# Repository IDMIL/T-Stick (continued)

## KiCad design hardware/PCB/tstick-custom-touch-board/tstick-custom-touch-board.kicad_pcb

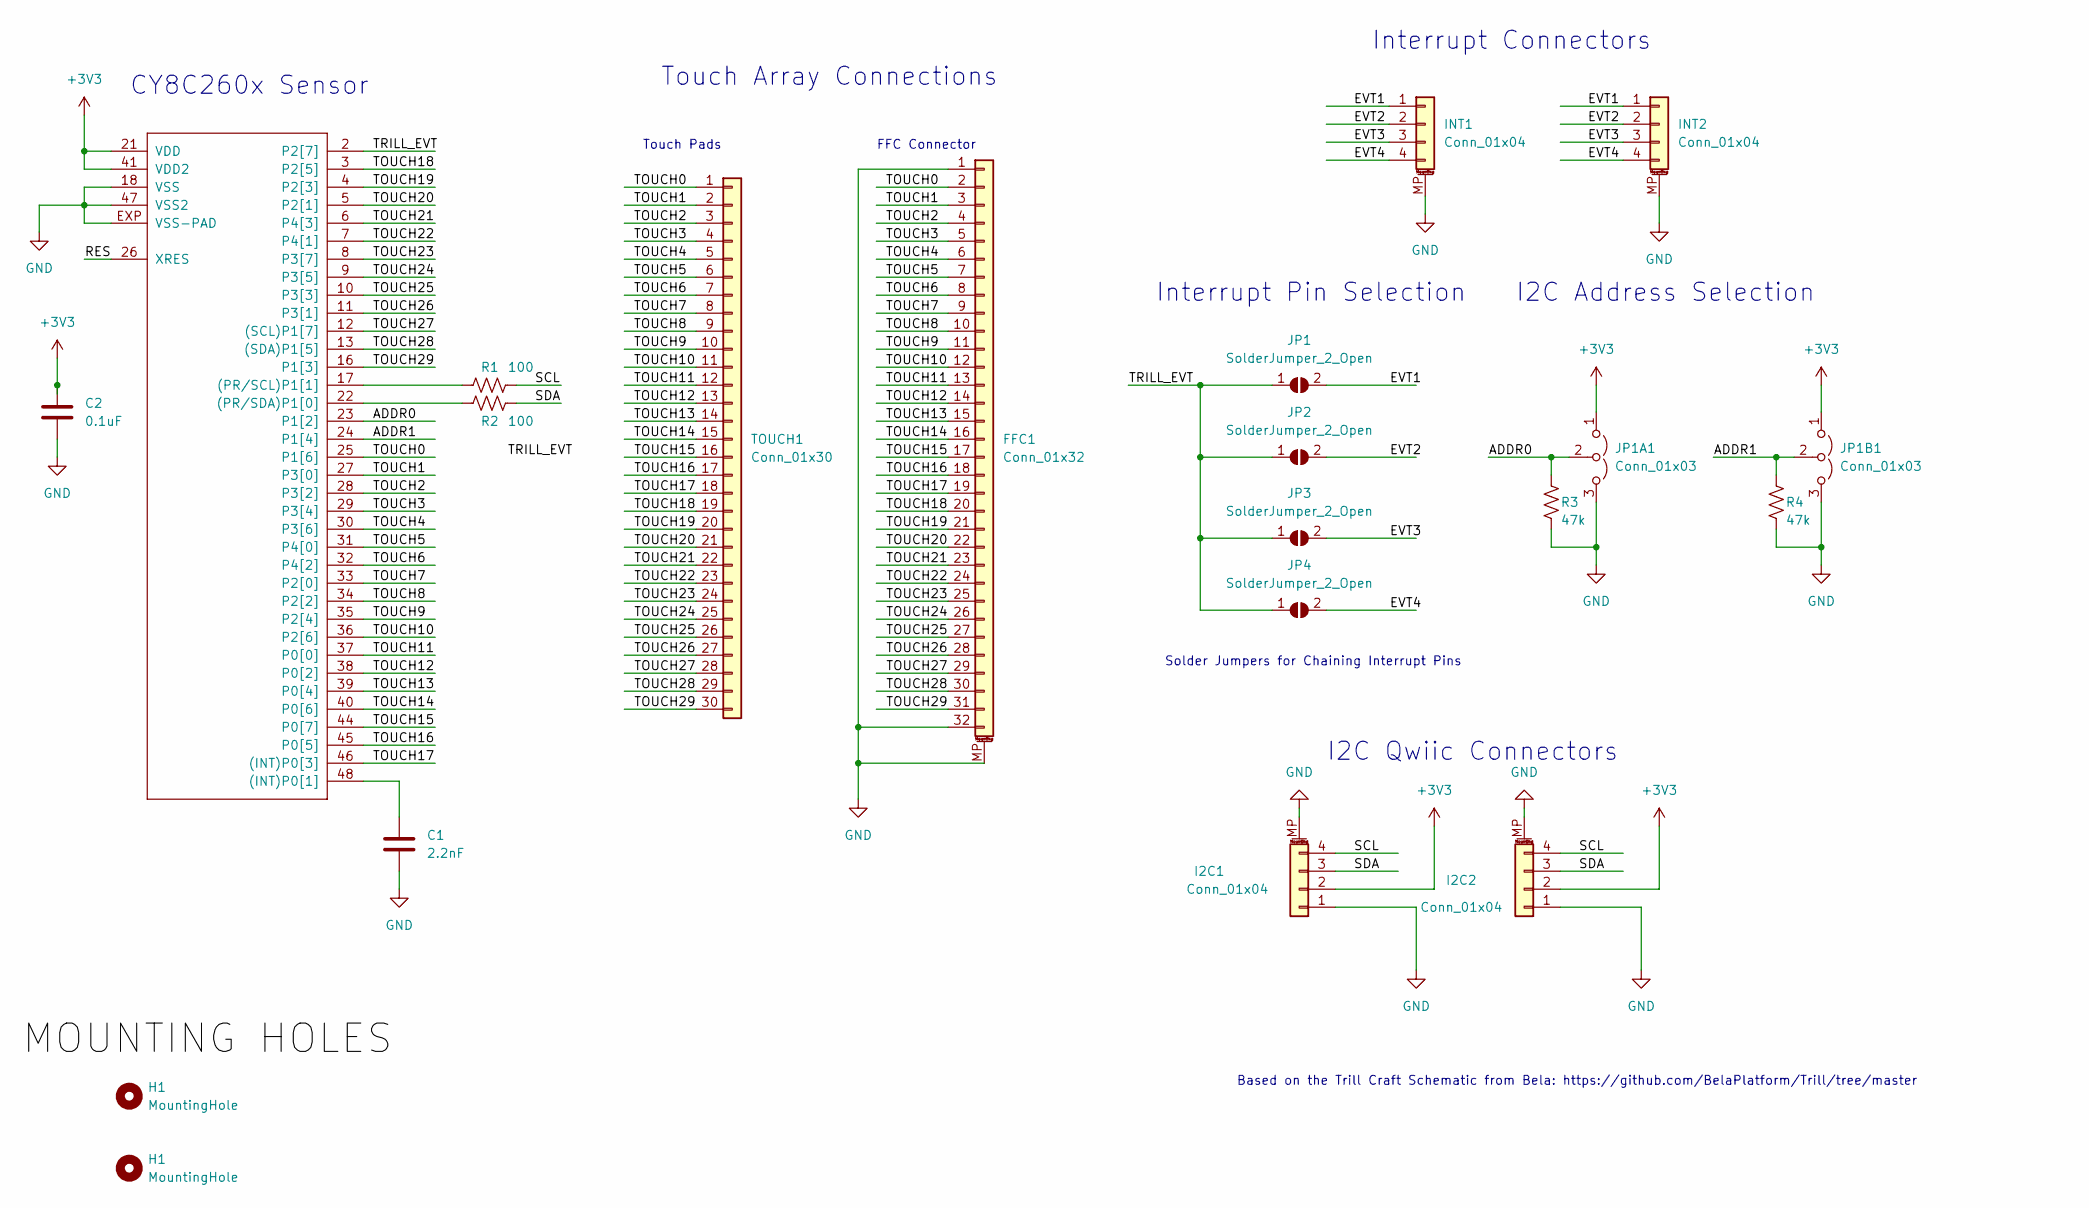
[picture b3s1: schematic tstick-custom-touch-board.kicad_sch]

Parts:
C1: 2.2nF; C_0603_1608Metric
C2: 0.1uF; C_0603_1608Metric
FFC1: Conn_01x32; CON_541323262_MOL; Mfg Part # 0541323262; Digikey Part # 900-0541323262CT-ND
H1: MountingHole; MountingHole_3.2mm_M3_DIN965
I2C1, I2C2: Conn_01x04; JST_SH_SM04B-SRSS-TB_1x04-1MP_P1.00mm_Horizontal
IC1: CY8C206X6A; QFN48-LEADS
INT1, INT2: Conn_01x04; JST_SH_SM04B-SRSS-TB_1x04-1MP_P1.00mm_Horizontal
JP1, JP2, JP3, JP4: SolderJumper_2_Open; SolderJumper-2_P1.3mm_Open_RoundedPad1.0x1.5mm
JP1A1, JP1B1: Conn_01x03; DOUBLE_SOLDER_JUMPER
R1, R2: 100; R_0603_1608Metric
R3, R4: 47k; R_0603_1608Metric
TOUCH1: Conn_01x30; TOUCHSENSORPAD; Mfg Part # 0541323262; Digikey Part # 900-0541323262CT-ND

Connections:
+3V3: C2.1, I2C1.2, I2C2.2, IC1.21 (VDD), IC1.41 (VDD2), JP1A1.1 (A), JP1B1.1 (A)
/ADDR0: IC1.23 (P1[2]), JP1A1.2 (C), R3.1
/ADDR1: IC1.24 (P1[4]), JP1B1.2 (C), R4.1
/EVT1: INT1.1, INT2.1, JP1.2 (B)
/EVT2: INT1.2, INT2.2, JP2.2 (B)
/EVT3: INT1.3, INT2.3, JP3.2 (B)
/EVT4: INT1.4, INT2.4, JP4.2 (B)
/RES: IC1.26 (XRES)
/SCL: I2C1.4, I2C2.4, R1.1
/SDA: I2C1.3, I2C2.3, R2.1
/TOUCH0: FFC1.2, IC1.25 (P1[6]), TOUCH1.1
/TOUCH1: FFC1.3, IC1.27 (P3[0]), TOUCH1.2
/TOUCH2: FFC1.4, IC1.28 (P3[2]), TOUCH1.3
/TOUCH3: FFC1.5, IC1.29 (P3[4]), TOUCH1.4
/TOUCH4: FFC1.6, IC1.30 (P3[6]), TOUCH1.5
/TOUCH5: FFC1.7, IC1.31 (P4[0]), TOUCH1.6
/TOUCH6: FFC1.8, IC1.32 (P4[2]), TOUCH1.7
/TOUCH7: FFC1.9, IC1.33 (P2[0]), TOUCH1.8
/TOUCH8: FFC1.10, IC1.34 (P2[2]), TOUCH1.9
/TOUCH9: FFC1.11, IC1.35 (P2[4]), TOUCH1.10
/TOUCH10: FFC1.12, IC1.36 (P2[6]), TOUCH1.11
/TOUCH11: FFC1.13, IC1.37 (P0[0]), TOUCH1.12
/TOUCH12: FFC1.14, IC1.38 (P0[2]), TOUCH1.13
/TOUCH13: FFC1.15, IC1.39 (P0[4]), TOUCH1.14
/TOUCH14: FFC1.16, IC1.40 (P0[6]), TOUCH1.15
/TOUCH15: FFC1.17, IC1.44 (P0[7]), TOUCH1.16
/TOUCH16: FFC1.18, IC1.45 (P0[5]), TOUCH1.17
/TOUCH17: FFC1.19, IC1.46 ((INT)P0[3]), TOUCH1.18
/TOUCH18: FFC1.20, IC1.3 (P2[5]), TOUCH1.19
/TOUCH19: FFC1.21, IC1.4 (P2[3]), TOUCH1.20
/TOUCH20: FFC1.22, IC1.5 (P2[1]), TOUCH1.21
/TOUCH21: FFC1.23, IC1.6 (P4[3]), TOUCH1.22
/TOUCH22: FFC1.24, IC1.7 (P4[1]), TOUCH1.23
/TOUCH23: FFC1.25, IC1.8 (P3[7]), TOUCH1.24
/TOUCH24: FFC1.26, IC1.9 (P3[5]), TOUCH1.25
/TOUCH25: FFC1.27, IC1.10 (P3[3]), TOUCH1.26
/TOUCH26: FFC1.28, IC1.11 (P3[1]), TOUCH1.27
/TOUCH27: FFC1.29, IC1.12 ((SCL)P1[7]), TOUCH1.28
/TOUCH28: FFC1.30, IC1.13 ((SDA)P1[5]), TOUCH1.29
/TOUCH29: FFC1.31, IC1.16 (P1[3]), TOUCH1.30
/TRILL_EVT: IC1.2 (P2[7]), JP1.1 (A), JP2.1 (A), JP3.1 (A), JP4.1 (A)
GND: C1.2, C2.2, FFC1.1, FFC1.32, FFC1.MP (MountPin), I2C1.1, I2C1.MP (MountPin), I2C2.1, I2C2.MP (MountPin), IC1.18 (VSS), IC1.47 (VSS2), IC1.EXP (VSS-PAD), INT1.MP (MountPin), INT2.MP (MountPin), JP1A1.3 (B), JP1B1.3 (B), R3.2, R4.2
unnamed: C1.1, IC1.48 ((INT)P0[1])
unnamed: IC1.17 ((PR/SCL)P1[1]), R1.2
unnamed: IC1.22 ((PR/SDA)P1[0]), R2.2

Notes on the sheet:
Solder Jumpers for Chaining Interrupt Pins
Touch Array Connections
Interrupt Connectors
Touch Pads
FFC Connector
I2C Address Selection
CY8C260x Sensor
Based on the Trill Craft Schematic from Bela: https://github.com/BelaPlatform/Trill/tree/master
Interrupt Pin Selection
I2C Qwiic Connectors

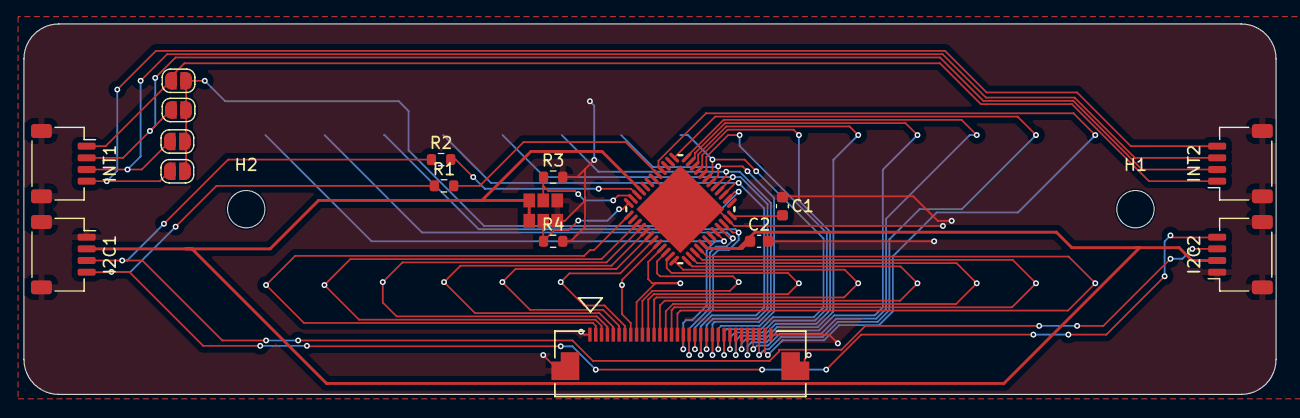
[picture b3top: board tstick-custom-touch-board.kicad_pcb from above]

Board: 2 copper layers, 107.3 x 31.8 mm, 21 parts (1 on the bottom side), 44 nets.

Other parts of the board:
H2: MountingHole; MountingHole_3.2mm_M3_DIN965

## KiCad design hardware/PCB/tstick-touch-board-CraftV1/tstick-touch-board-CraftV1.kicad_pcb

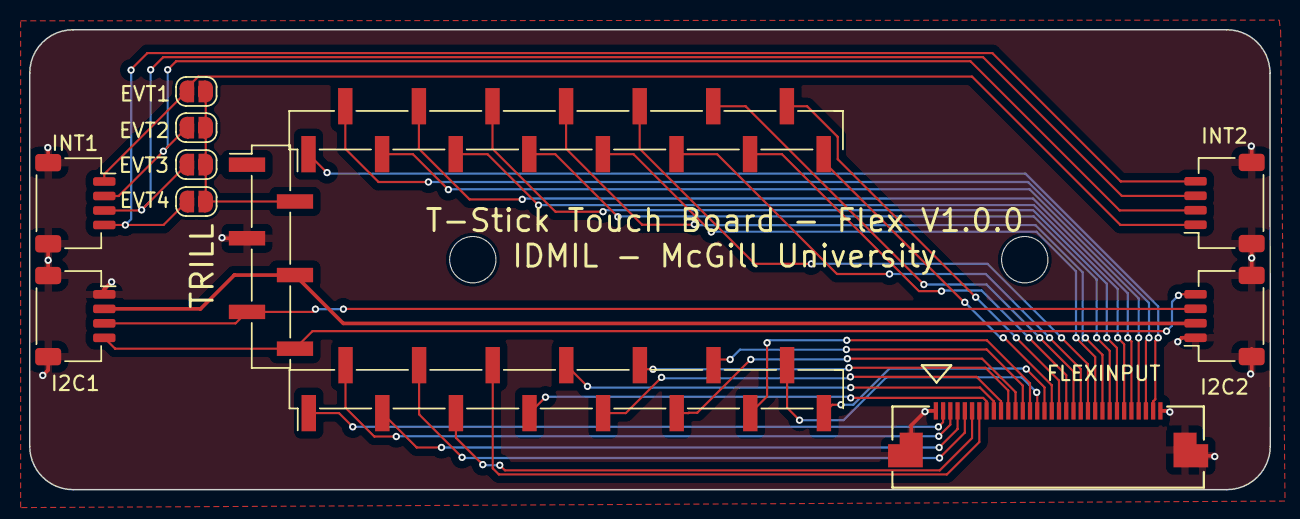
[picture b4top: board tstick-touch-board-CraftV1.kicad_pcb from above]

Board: 2 copper layers, 85.6 x 31.8 mm, 14 parts (0 on the bottom side), 39 nets.

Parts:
H1, H2: MountingHole; MountingHole_3.2mm_M3_DIN965
I2C1, I2C2: Conn_01x04; JST_SH_SM04B-SRSS-TB_1x04-1MP_P1.00mm_Horizontal
INT1, INT2: Conn_01x04; JST_SH_SM04B-SRSS-TB_1x04-1MP_P1.00mm_Horizontal
J1: Conn_01x32; CON_541323262_MOL
JP1, JP2, JP3, JP4: SolderJumper_2_Open; SolderJumper-2_P1.3mm_Open_RoundedPad1.0x1.5mm
TOUCH1, TOUCH2: Conn_01x15; PinHeader_1x15_P2.54mm_Vertical_SMD_Pin1Left
TOUCH3: Conn_01x06; PinHeader_1x06_P2.54mm_Vertical_SMD_Pin1Left

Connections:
+3V3: I2C1.2, I2C2.2, TOUCH3.4
/EVT1: INT1.1, INT2.1, JP1.2 (B)
/EVT2: INT1.2, INT2.2, JP2.2 (B)
/EVT3: INT1.3, INT2.3, JP3.2 (B)
/EVT4: INT1.4, INT2.4, JP4.2 (B)
/SCL: I2C1.4, I2C2.4, TOUCH3.6
/SDA: I2C1.3, I2C2.3, TOUCH3.5
/TOUCH0: J1.2, TOUCH1.1
/TOUCH1: J1.3, TOUCH1.2
/TOUCH2: J1.4, TOUCH1.3
/TOUCH3: J1.5, TOUCH1.4
/TOUCH4: J1.6, TOUCH1.5
/TOUCH5: J1.7, TOUCH1.6
/TOUCH6: J1.8, TOUCH1.7
/TOUCH7: J1.9, TOUCH1.8
/TOUCH8: J1.10, TOUCH1.9
/TOUCH9: J1.11, TOUCH1.10
/TOUCH10: J1.12, TOUCH1.11
/TOUCH11: J1.13, TOUCH1.12
/TOUCH12: J1.14, TOUCH1.13
/TOUCH13: J1.15, TOUCH1.14
/TOUCH14: J1.16, TOUCH1.15
/TOUCH15: J1.17, TOUCH2.15
/TOUCH16: J1.18, TOUCH2.14
/TOUCH17: J1.19, TOUCH2.13
/TOUCH18: J1.20, TOUCH2.12
/TOUCH19: J1.21, TOUCH2.11
/TOUCH20: J1.22, TOUCH2.10
/TOUCH21: J1.23, TOUCH2.9
/TOUCH22: J1.24, TOUCH2.8
/TOUCH23: J1.25, TOUCH2.7
/TOUCH24: J1.26, TOUCH2.6
/TOUCH25: J1.27, TOUCH2.5
/TOUCH26: J1.28, TOUCH2.4
/TOUCH27: J1.29, TOUCH2.3
/TOUCH28: J1.30, TOUCH2.2
/TOUCH29: J1.31, TOUCH2.1
/TRILL_EVT: JP1.1 (A), JP2.1 (A), JP3.1 (A), JP4.1 (A), TOUCH3.2
GND: I2C1.1, I2C1.MP (MountPin), I2C2.1, I2C2.MP (MountPin), INT1.MP (MountPin), INT2.MP (MountPin), J1.1, J1.32, J1.MP (MountPin), TOUCH3.3

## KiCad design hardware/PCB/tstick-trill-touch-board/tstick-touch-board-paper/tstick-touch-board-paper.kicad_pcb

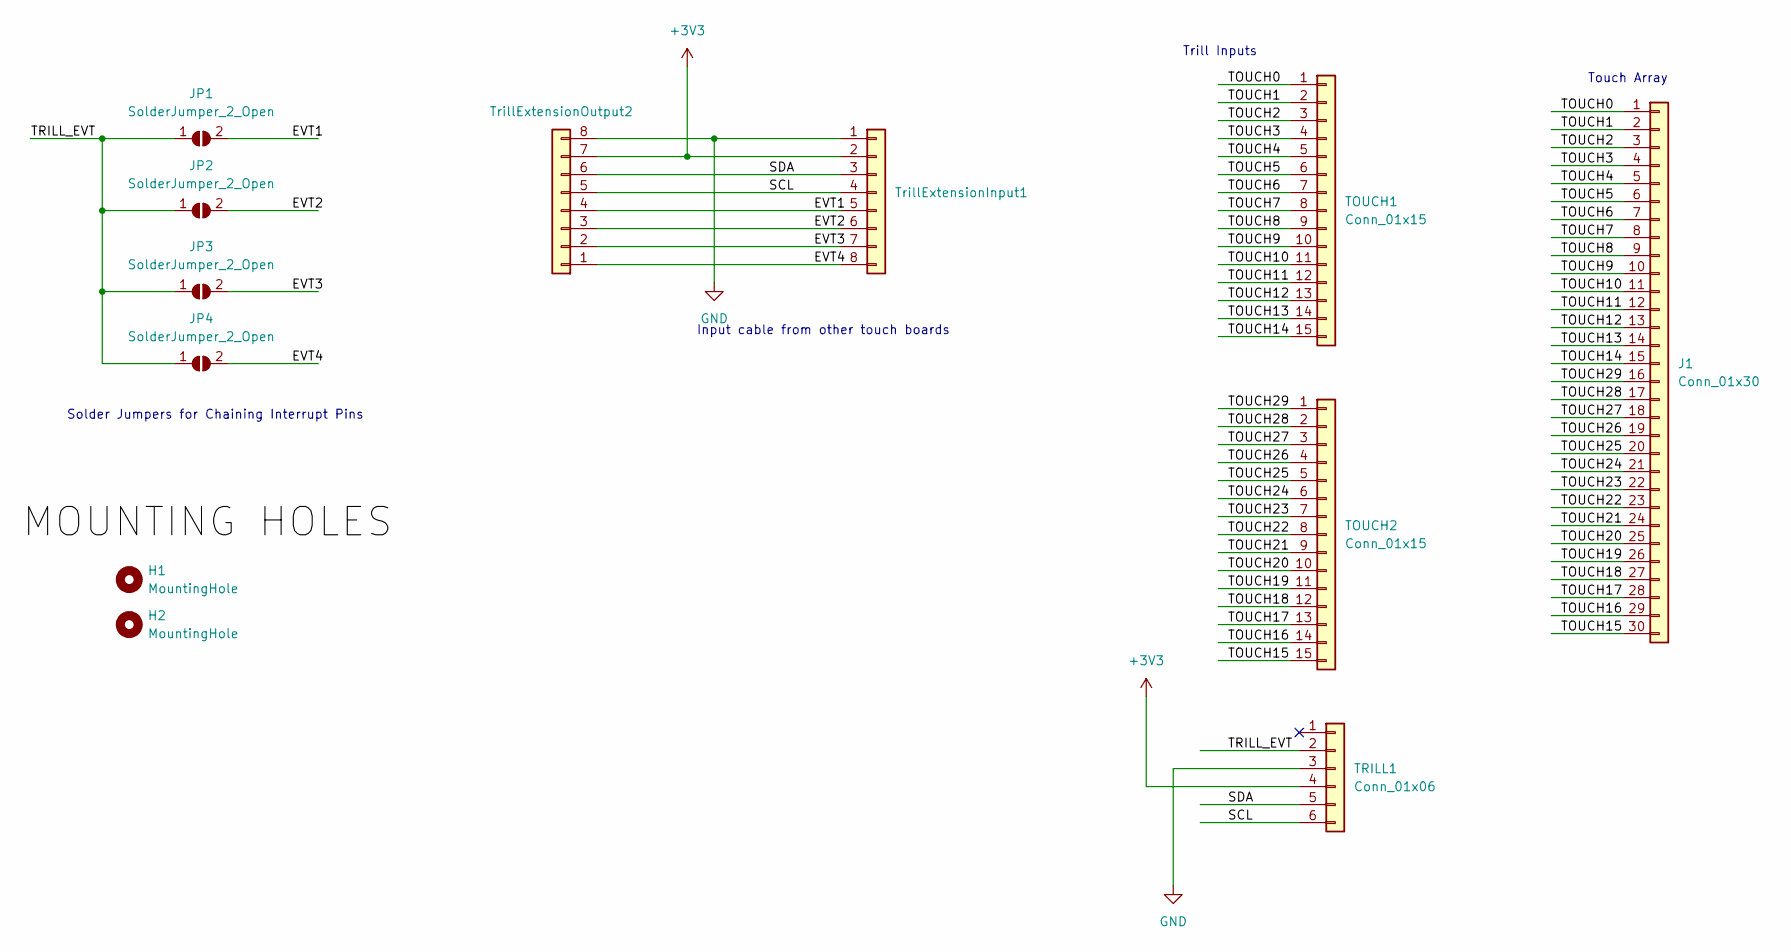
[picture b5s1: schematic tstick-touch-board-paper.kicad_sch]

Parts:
H1, H2: MountingHole; MountingHole_3.2mm_M3_DIN965
J1: Conn_01x30; TOUCHSENSORPAD
JP1, JP2, JP3, JP4: SolderJumper_2_Open; SolderJumper-2_P1.3mm_Open_RoundedPad1.0x1.5mm
TOUCH1, TOUCH2: Conn_01x15; PinHeader_1x15_P2.54mm_Vertical_SMD_Pin1Left
TRILL1: Conn_01x06; PinHeader_1x06_P2.54mm_Vertical_SMD_Pin1Left
TrillExtensionInput1: Conn_01x08; JST_SHL_SM08B-SHLS-TF_1x08-1MP_P1.00mm_Horizontal; Digikey Part # 455-3960-1-ND
TrillExtensionOutput2: Conn_01x08; JST_SHL_SM08B-SHLS-TF_1x08-1MP_P1.00mm_Horizontal; Digikey Part # 455-3960-1-ND

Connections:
+3V3: TRILL1.4, TrillExtensionInput1.2, TrillExtensionOutput2.7
/EVT1: JP1.2 (B), TrillExtensionInput1.5, TrillExtensionOutput2.4
/EVT2: JP2.2 (B), TrillExtensionInput1.6, TrillExtensionOutput2.3
/EVT3: JP3.2 (B), TrillExtensionInput1.7, TrillExtensionOutput2.2
/EVT4: JP4.2 (B), TrillExtensionInput1.8, TrillExtensionOutput2.1
/SCL: TRILL1.6, TrillExtensionInput1.4, TrillExtensionOutput2.5
/SDA: TRILL1.5, TrillExtensionInput1.3, TrillExtensionOutput2.6
/TOUCH0: TOUCH1.1; also elsewhere on the board
/TOUCH1: TOUCH1.2; also elsewhere on the board
/TOUCH2: TOUCH1.3; also elsewhere on the board
/TOUCH3: TOUCH1.4; also elsewhere on the board
/TOUCH4: TOUCH1.5; also elsewhere on the board
/TOUCH5: TOUCH1.6; also elsewhere on the board
/TOUCH6: TOUCH1.7; also elsewhere on the board
/TOUCH7: TOUCH1.8; also elsewhere on the board
/TOUCH8: TOUCH1.9; also elsewhere on the board
/TOUCH9: TOUCH1.10; also elsewhere on the board
/TOUCH10: TOUCH1.11; also elsewhere on the board
/TOUCH11: TOUCH1.12; also elsewhere on the board
/TOUCH12: TOUCH1.13; also elsewhere on the board
/TOUCH13: TOUCH1.14; also elsewhere on the board
/TOUCH14: TOUCH1.15; also elsewhere on the board
/TOUCH15: TOUCH2.15; also elsewhere on the board
/TOUCH16: TOUCH2.14; also elsewhere on the board
/TOUCH17: TOUCH2.13; also elsewhere on the board
/TOUCH18: TOUCH2.12; also elsewhere on the board
/TOUCH19: TOUCH2.11; also elsewhere on the board
/TOUCH20: TOUCH2.10; also elsewhere on the board
/TOUCH21: TOUCH2.9; also elsewhere on the board
/TOUCH22: TOUCH2.8; also elsewhere on the board
/TOUCH23: TOUCH2.7; also elsewhere on the board
/TOUCH24: TOUCH2.6; also elsewhere on the board
/TOUCH25: TOUCH2.5; also elsewhere on the board
/TOUCH26: TOUCH2.4; also elsewhere on the board
/TOUCH27: TOUCH2.3; also elsewhere on the board
/TOUCH28: TOUCH2.2; also elsewhere on the board
/TOUCH29: TOUCH2.1; also elsewhere on the board
/TRILL_EVT: JP1.1 (A), JP2.1 (A), JP3.1 (A), JP4.1 (A), TRILL1.2
GND: TRILL1.3, TrillExtensionInput1.1, TrillExtensionOutput2.8

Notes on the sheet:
Touch Array
Input cable from other touch boards
Trill Inputs
Solder Jumpers for Chaining Interrupt Pins

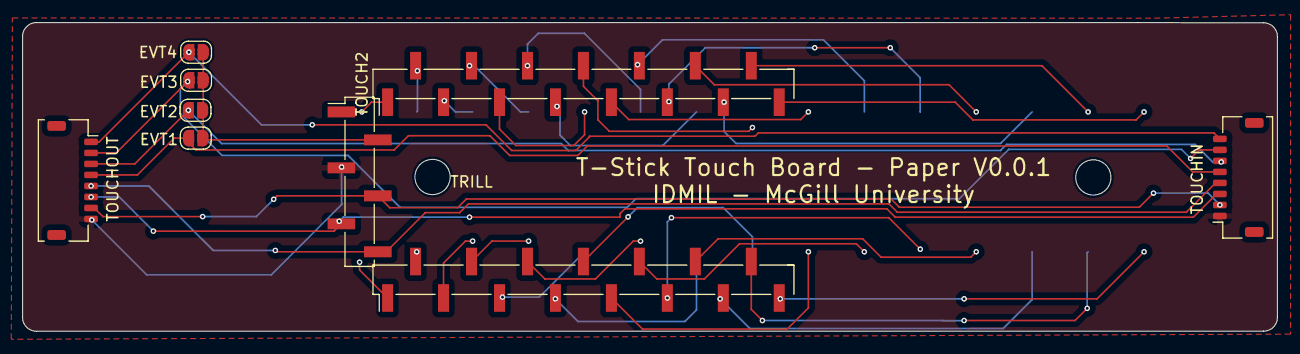
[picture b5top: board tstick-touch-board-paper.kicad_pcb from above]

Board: 2 copper layers, 113.9 x 28.0 mm, 12 parts (1 on the bottom side), 39 nets.

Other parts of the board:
TOUCHPADS1: Conn_01x30; TOUCHSENSORPAD

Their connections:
/TOUCH0: TOUCHPADS1.1; also elsewhere on the board
/TOUCH1: TOUCHPADS1.2; also elsewhere on the board
/TOUCH2: TOUCHPADS1.3; also elsewhere on the board
/TOUCH3: TOUCHPADS1.4; also elsewhere on the board
/TOUCH4: TOUCHPADS1.5; also elsewhere on the board
/TOUCH5: TOUCHPADS1.6; also elsewhere on the board
/TOUCH6: TOUCHPADS1.7; also elsewhere on the board
/TOUCH7: TOUCHPADS1.8; also elsewhere on the board
/TOUCH8: TOUCHPADS1.9; also elsewhere on the board
/TOUCH9: TOUCHPADS1.10; also elsewhere on the board
/TOUCH10: TOUCHPADS1.11; also elsewhere on the board
/TOUCH11: TOUCHPADS1.12; also elsewhere on the board
/TOUCH12: TOUCHPADS1.13; also elsewhere on the board
/TOUCH13: TOUCHPADS1.14; also elsewhere on the board
/TOUCH14: TOUCHPADS1.15; also elsewhere on the board
/TOUCH15: TOUCHPADS1.30; also elsewhere on the board
/TOUCH16: TOUCHPADS1.29; also elsewhere on the board
/TOUCH17: TOUCHPADS1.28; also elsewhere on the board
/TOUCH18: TOUCHPADS1.27; also elsewhere on the board
/TOUCH19: TOUCHPADS1.26; also elsewhere on the board
/TOUCH20: TOUCHPADS1.25; also elsewhere on the board
/TOUCH21: TOUCHPADS1.24; also elsewhere on the board
/TOUCH22: TOUCHPADS1.23; also elsewhere on the board
/TOUCH23: TOUCHPADS1.22; also elsewhere on the board
/TOUCH24: TOUCHPADS1.21; also elsewhere on the board
/TOUCH25: TOUCHPADS1.20; also elsewhere on the board
/TOUCH26: TOUCHPADS1.19; also elsewhere on the board
/TOUCH27: TOUCHPADS1.18; also elsewhere on the board
/TOUCH28: TOUCHPADS1.17; also elsewhere on the board
/TOUCH29: TOUCHPADS1.16; also elsewhere on the board
